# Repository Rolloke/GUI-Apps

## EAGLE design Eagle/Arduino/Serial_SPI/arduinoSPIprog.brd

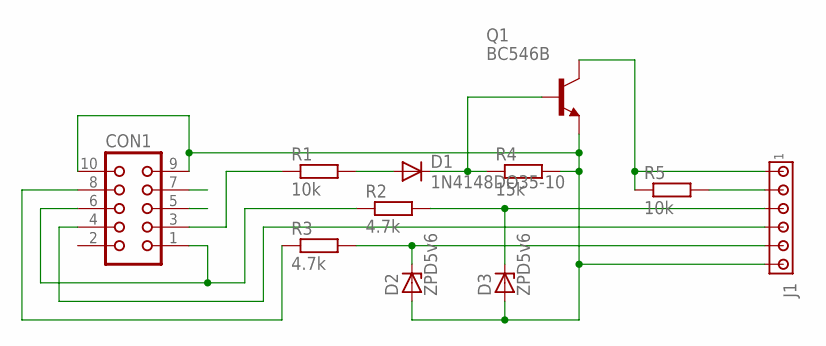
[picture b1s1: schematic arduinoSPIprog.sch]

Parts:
CON1: CON10
D1: 1N4148DO35-10; DO35-10
D2, D3: ZPD5v6; DO35Z10
J1: MTA06-100; 10X06MTA
Q1: BC546B; TO92-EBC
R1, R5: 10k; 0207/10
R2, R3: 4.7k; 0207/10
R4: 15k; 0207/10

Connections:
5V: J1.5 (2), R5.2
CTS/MISO: CON1.4, J1.3 (4)
DSR+RTS/SCK: CON1.1, CON1.6, R2.1
DTR/MOSI: CON1.8, R3.1
GND: CON1.9, CON1.10, D2.A, D3.A, J1.1 (6), Q1.E, R4.2
MOSI: D2.C, J1.2 (5), R3.2
unnamed: D1.A, R1.2
unnamed: D1.C, Q1.B, R4.1
RESET: J1.6 (1), Q1.C, R5.1
RI: CON1.7
RXD: CON1.5
SCK: D3.C, J1.4 (3), R2.2
TXD/RESET: CON1.3, R1.1

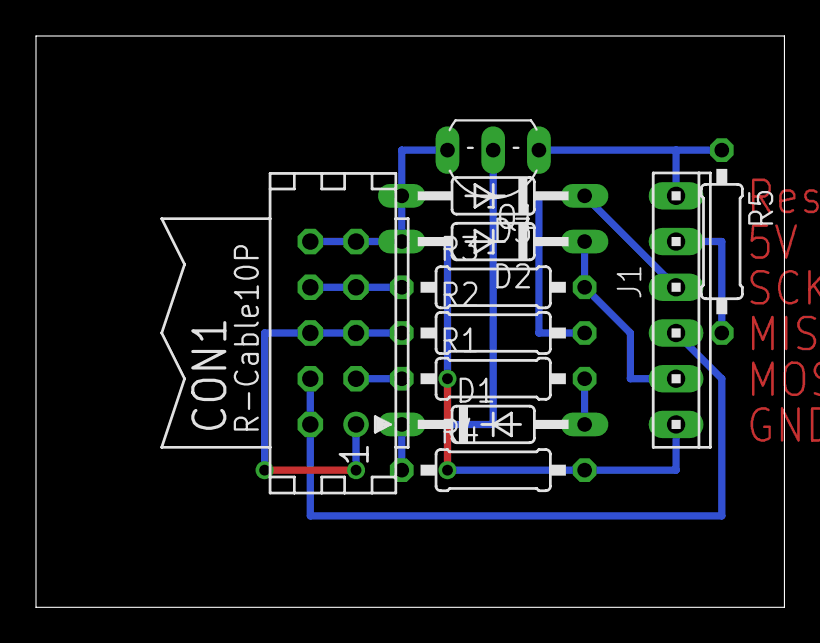
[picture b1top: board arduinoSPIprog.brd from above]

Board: 2 copper layers, 41.6 x 31.7 mm, 11 parts (0 on the bottom side), 11 nets.

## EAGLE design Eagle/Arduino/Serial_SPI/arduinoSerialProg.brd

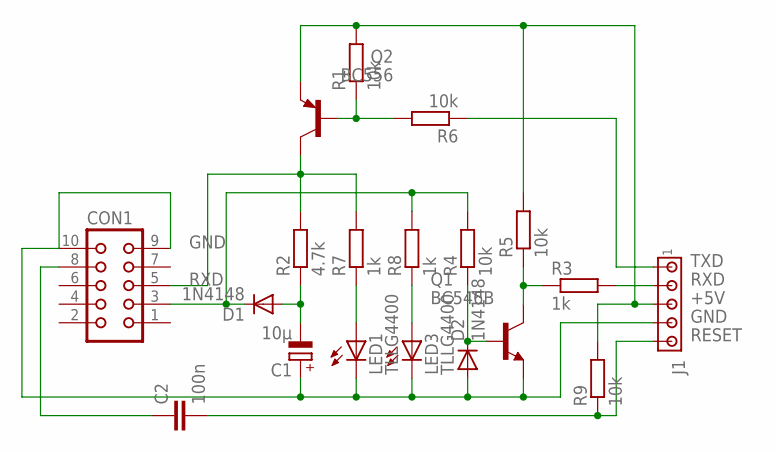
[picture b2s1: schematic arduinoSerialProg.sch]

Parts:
C1: 10µ; E2,5-6E
C2: 100n; C050-025X075
CON1: CON10
D1, D2: 1N4148; DO35-10
J1: MTA05-100; 10X05MTA
LED1, LED3: TLLG4400; LED3MM
Q1: BC546B; TO92-EBC
Q2: BC556; TO92-EBC
R1, R5: 10k; 0204V
R2: 4.7k; 0207/10
R3, R7, R8: 1k; 0207/10
R4, R6, R9: 10k; 0207/10

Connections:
+5V: J1.3, Q2.E, R1.2, R5.2, R9.2
DTR: C2.1, CON1.8
GND: C1.+, CON1.9, CON1.10, D2.A, J1.4, LED1.K (C), LED3.K (C), Q1.E
unnamed: LED1.A, R7.1
unnamed: C1.-, D1.A, R2.1
unnamed: LED3.A, R8.1
unnamed: Q2.B, R1.1, R6.2
unnamed: Q1.C, R3.1, R5.1
unnamed: D2.C, Q1.B, R4.1
RESET: C2.2, J1.5, R9.1
RXD: CON1.5, J1.2, Q2.C, R2.2, R3.2, R7.2
TXD: CON1.3, D1.C, J1.1, R4.2, R6.1, R8.2

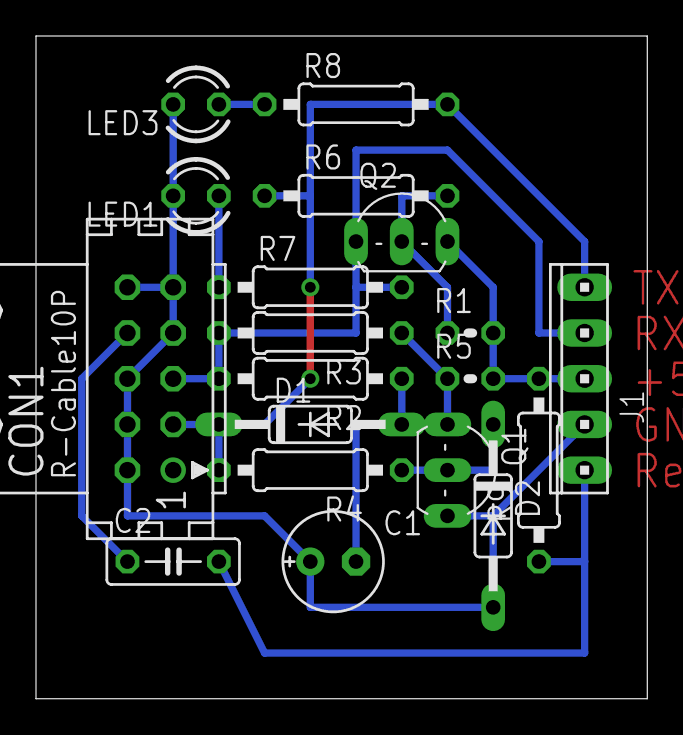
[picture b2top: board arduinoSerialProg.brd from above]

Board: 2 copper layers, 34.0 x 36.8 mm, 19 parts (0 on the bottom side), 12 nets.

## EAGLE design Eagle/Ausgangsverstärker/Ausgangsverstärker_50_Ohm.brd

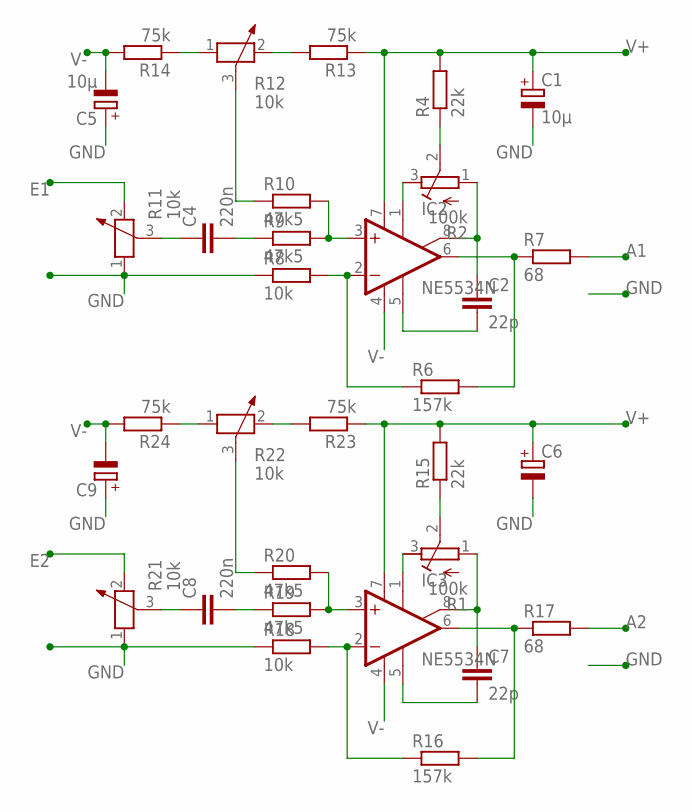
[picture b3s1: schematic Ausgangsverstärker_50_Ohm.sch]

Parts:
C1, C5: 10µ; E2-5
C2, C7: 22p; C050-024X044
C4, C8: 220n; C050-024X044
C6, C9: CPOL-EUE2-5; E2-5
IC2, IC3: NE5534N; DIL08
R1, R2: 100k; RTRIM64W
R4, R15: 22k; 0207/12
R6, R16: 157k; 0207/12
R7, R17: 68; 0207/12
R8, R18: 10k; 0207/12
R9, R10, R19, R20: 47k5; 0207/12
R11, R12, R21, R22: 10k; PT-10
R13, R14, R23, R24: 75k; 0207/12

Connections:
A1: R7.2
A2: R17.2
E1: R11.2
E2: R21.2
GND: C1.-, C5.+, C6.-, C9.+, R8.1, R11.1, R18.1, R21.1
unnamed: R2.2 (S), R4.1
unnamed: IC2.1 (ON), R2.3 (E)
unnamed: C2.1, IC2.8 (ON/CMP), R2.1 (A)
unnamed: C2.2, IC2.5 (CMP)
unnamed: IC2.3 (+IN), R9.2, R10.2
unnamed: C4.2, R9.1
unnamed: R10.1, R12.3
unnamed: IC2.2 (-IN), R6.1, R8.2
unnamed: C4.1, R11.3
unnamed: IC2.6 (OUT), R6.2, R7.1
unnamed: R12.2, R13.2
unnamed: R1.2 (S), R15.1
unnamed: C7.1, IC3.8 (ON/CMP), R1.1 (A)
unnamed: R12.1, R14.1
unnamed: C7.2, IC3.5 (CMP)
unnamed: IC3.1 (ON), R1.3 (E)
unnamed: IC3.3 (+IN), R19.2, R20.2
unnamed: C8.2, R19.1
unnamed: R20.1, R22.3
unnamed: IC3.2 (-IN), R16.1, R18.2
unnamed: IC3.6 (OUT), R16.2, R17.1
unnamed: R22.2, R23.2
unnamed: R22.1, R24.1
unnamed: C8.1, R21.3
V+: C1.+, C6.+, IC2.7 (V+), IC3.7 (V+), R4.2, R13.1, R15.2, R23.1
V-: C5.-, C9.-, IC2.4 (V-), IC3.4 (V-), R14.2, R24.2

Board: 2 copper layers, 32 parts (0 on the bottom side), 27 nets, no tracks yet.

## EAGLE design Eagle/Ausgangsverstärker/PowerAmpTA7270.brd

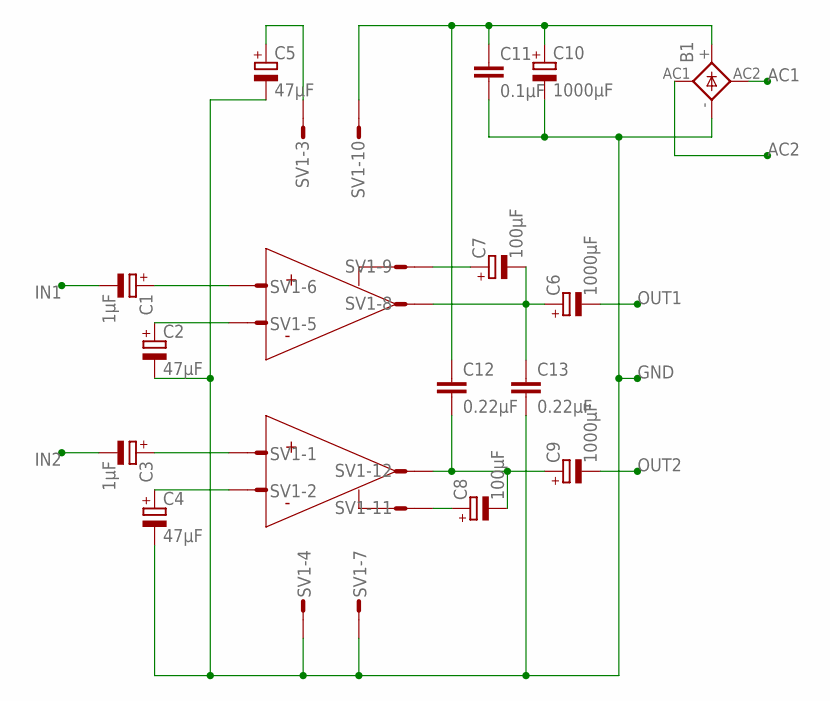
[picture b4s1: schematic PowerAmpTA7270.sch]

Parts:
B1: FB15A
C1, C3: 1µF; E15-5
C2, C4, C5: 47µF; B45181B
C6, C9: 1000µF; E5-13
C7, C8: 100µF; E3,5-10
C10: 1000µF; E45-18
C11: 0.1µF; C050-025X075
C12, C13: 0.22µF; C050-025X075
SV1: S12P

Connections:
AC1: B1.AC2
AC2: B1.AC1
GND: B1.-, C2.-, C4.-, C5.-, C10.-, C11.2, C13.2, SV1.4, SV1.7
IN1: C1.-
IN2: C3.-
unnamed: C7.+, SV1.9
unnamed: C6.+, C7.-, C13.1, SV1.8
unnamed: C8.-, C9.+, C12.2, SV1.12
unnamed: C8.+, SV1.11
unnamed: C3.+, SV1.1
unnamed: C4.+, SV1.2
unnamed: C1.+, SV1.6
unnamed: C2.+, SV1.5
unnamed: C5.+, SV1.3
OUT1: C6.-
OUT2: C9.-
VCC: B1.+, C10.+, C11.1, C12.1, SV1.10

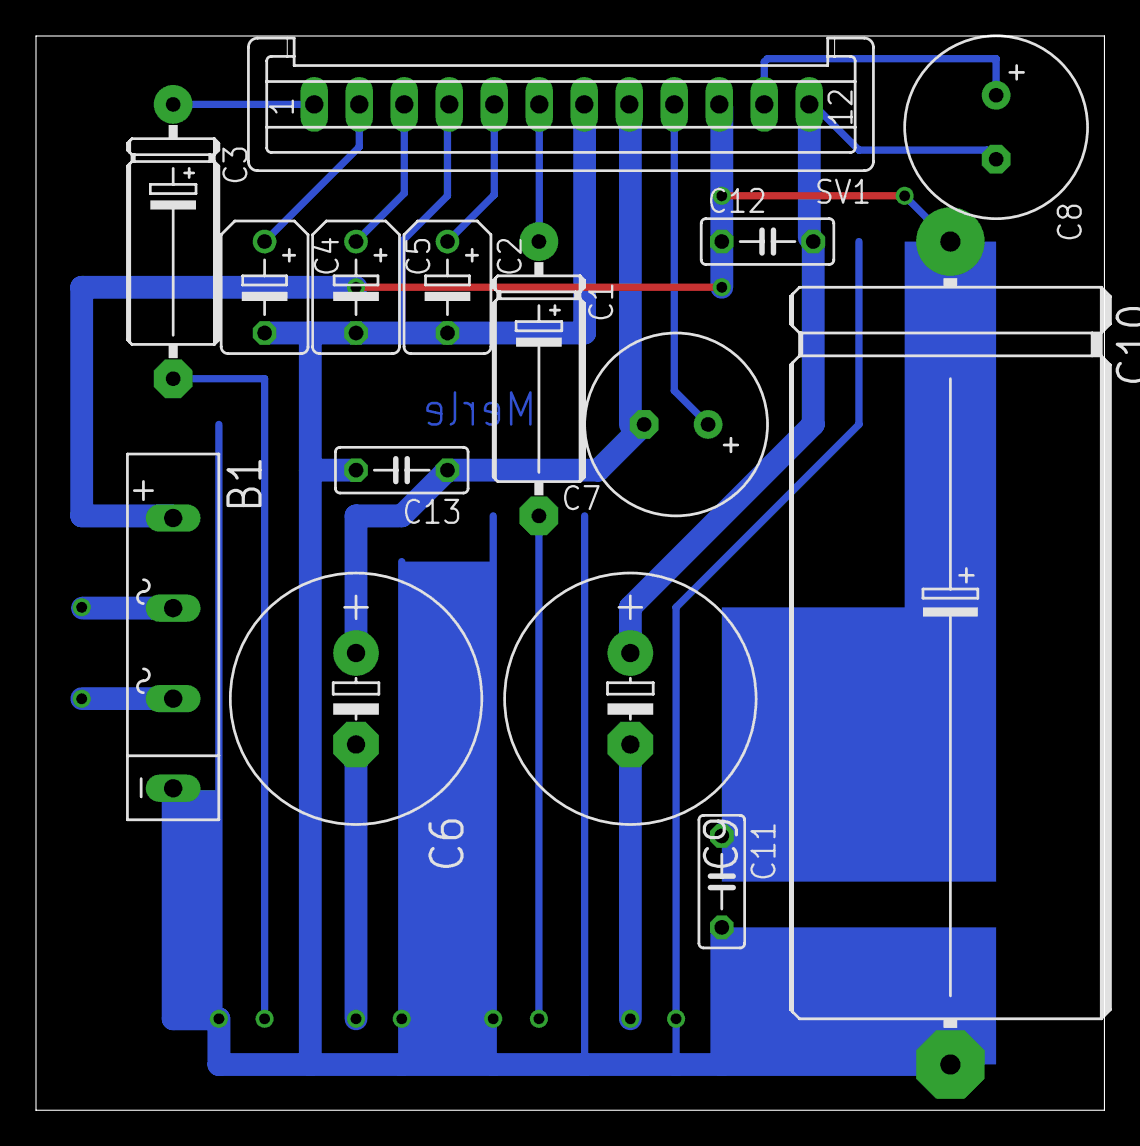
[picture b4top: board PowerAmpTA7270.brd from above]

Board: 2 copper layers, 59.4 x 59.7 mm, 15 parts (0 on the bottom side), 11 nets.

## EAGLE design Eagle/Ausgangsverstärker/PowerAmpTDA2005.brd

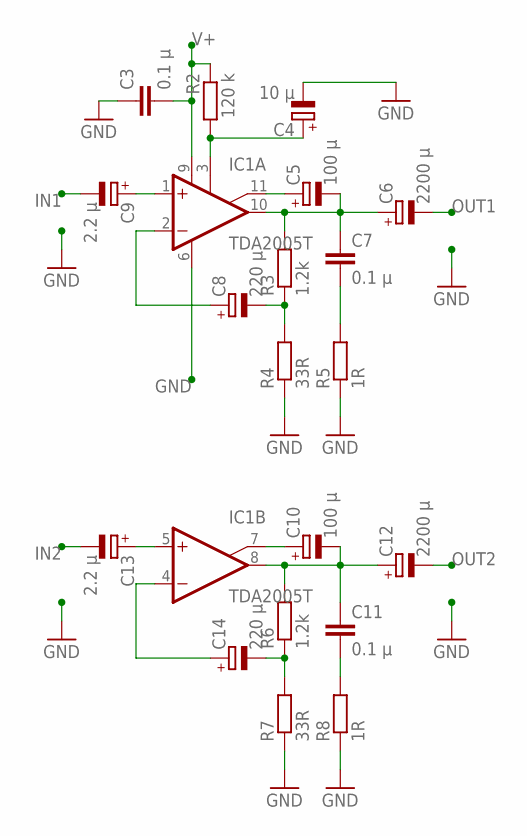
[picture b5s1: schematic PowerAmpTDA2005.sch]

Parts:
C3, C7, C11: 0.1 µ; C075-042X103
C4: 10 µ; E2,5-5
C5, C10: 100 µ; E3,5-8
C6, C12: 2200 µ; E5-13
C8, C14: 220 µ; E25-10
C9, C13: 2.2 µ; E2-5
IC1: TDA2005T; SIP11
R2: 120 k; 0207/12
R3, R6: 1.2k; 0207/12
R4, R7: 33R; 0207/12
R5, R8: 1R; 0207/12

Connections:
GND: C3.1, C4.-, IC1.6 (GND), R4.1, R5.1, R7.1, R8.1
IN1: C9.-
IN2: C13.-
unnamed: C4.+, IC1.3 (SVRR), R2.2
unnamed: C5.+, IC1.11 (BTSP)
unnamed: C5.-, C6.+, C7.1, IC1.10 (OUT), R3.2
unnamed: C8.-, R3.1, R4.2
unnamed: C7.2, R5.2
unnamed: C8.+, IC1.2 (-IN)
unnamed: C9.+, IC1.1 (+IN)
unnamed: C13.+, IC1.5 (+IN)
unnamed: C14.+, IC1.4 (-IN)
unnamed: C10.+, IC1.7 (BTSP)
unnamed: C10.-, C11.1, C12.+, IC1.8 (OUT), R6.2
unnamed: C14.-, R6.1, R7.2
unnamed: C11.2, R8.2
OUT1: C6.-
OUT2: C12.-
V+: C3.2, IC1.9 (V+), R2.1

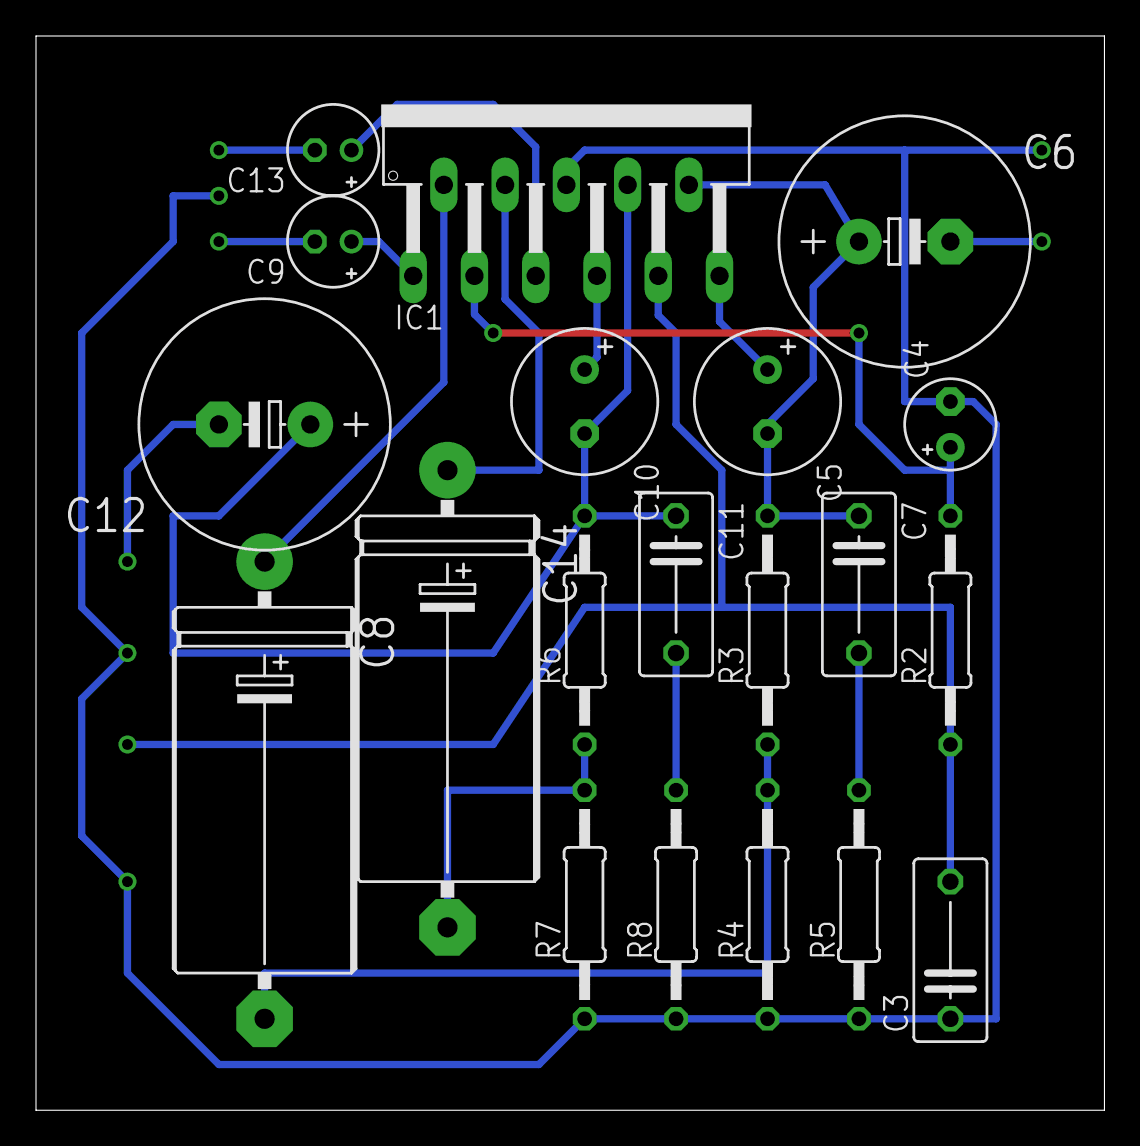
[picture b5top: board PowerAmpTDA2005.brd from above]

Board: 2 copper layers, 59.4 x 59.7 mm, 20 parts (0 on the bottom side), 15 nets.

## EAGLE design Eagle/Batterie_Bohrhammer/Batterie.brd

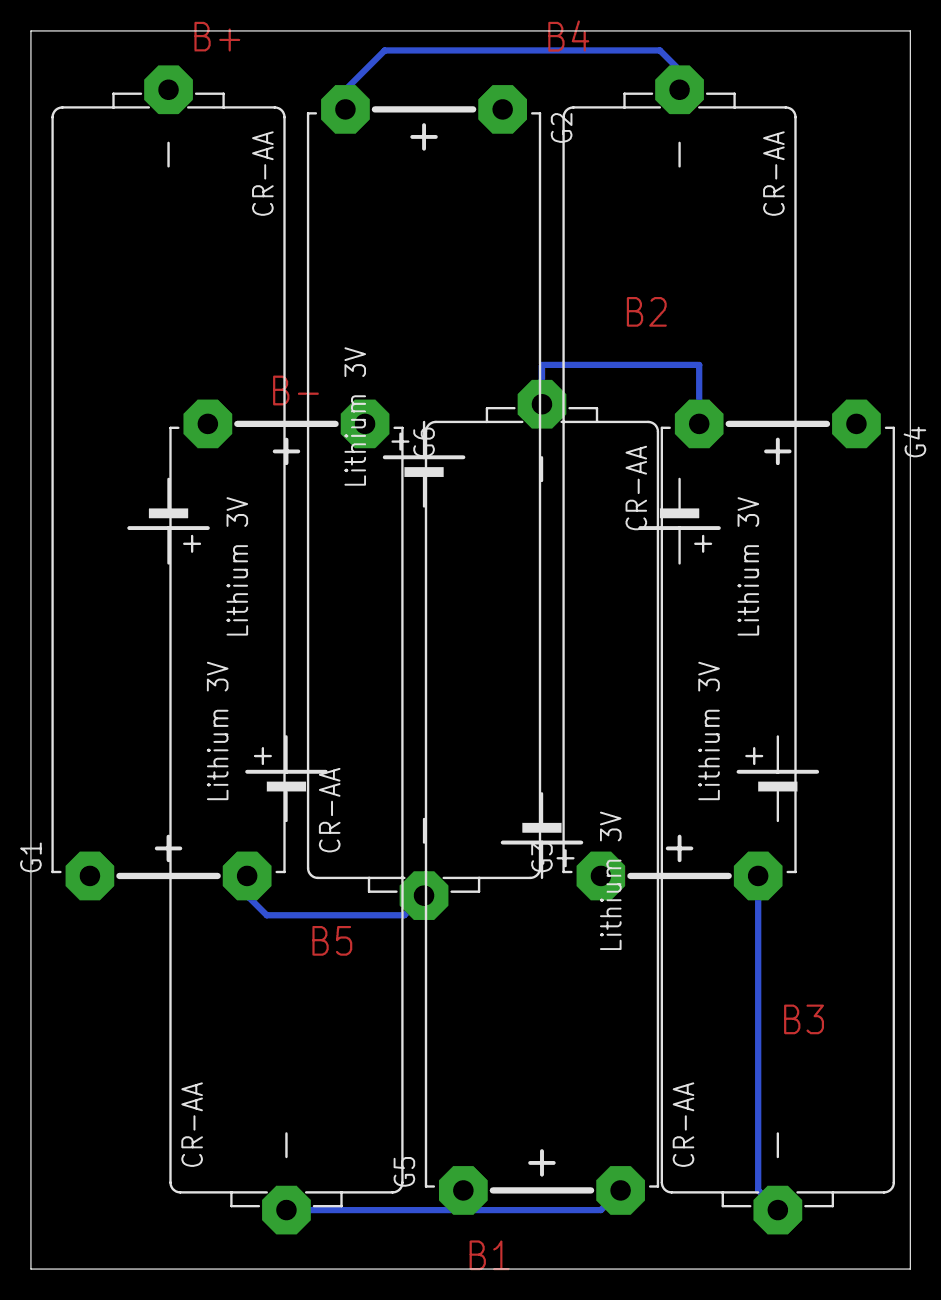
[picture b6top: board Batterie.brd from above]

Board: 2 copper layers, 56.8 x 80.0 mm, 6 parts (0 on the bottom side), 5 nets.

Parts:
G1, G2, G3, G4, G5, G6: CRAA

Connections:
unnamed: G1.+, G2.-
unnamed: G2.+, G3.-
unnamed: G3.+, G4.-
unnamed: G4.+, G5.-
unnamed: G5.+, G6.-
